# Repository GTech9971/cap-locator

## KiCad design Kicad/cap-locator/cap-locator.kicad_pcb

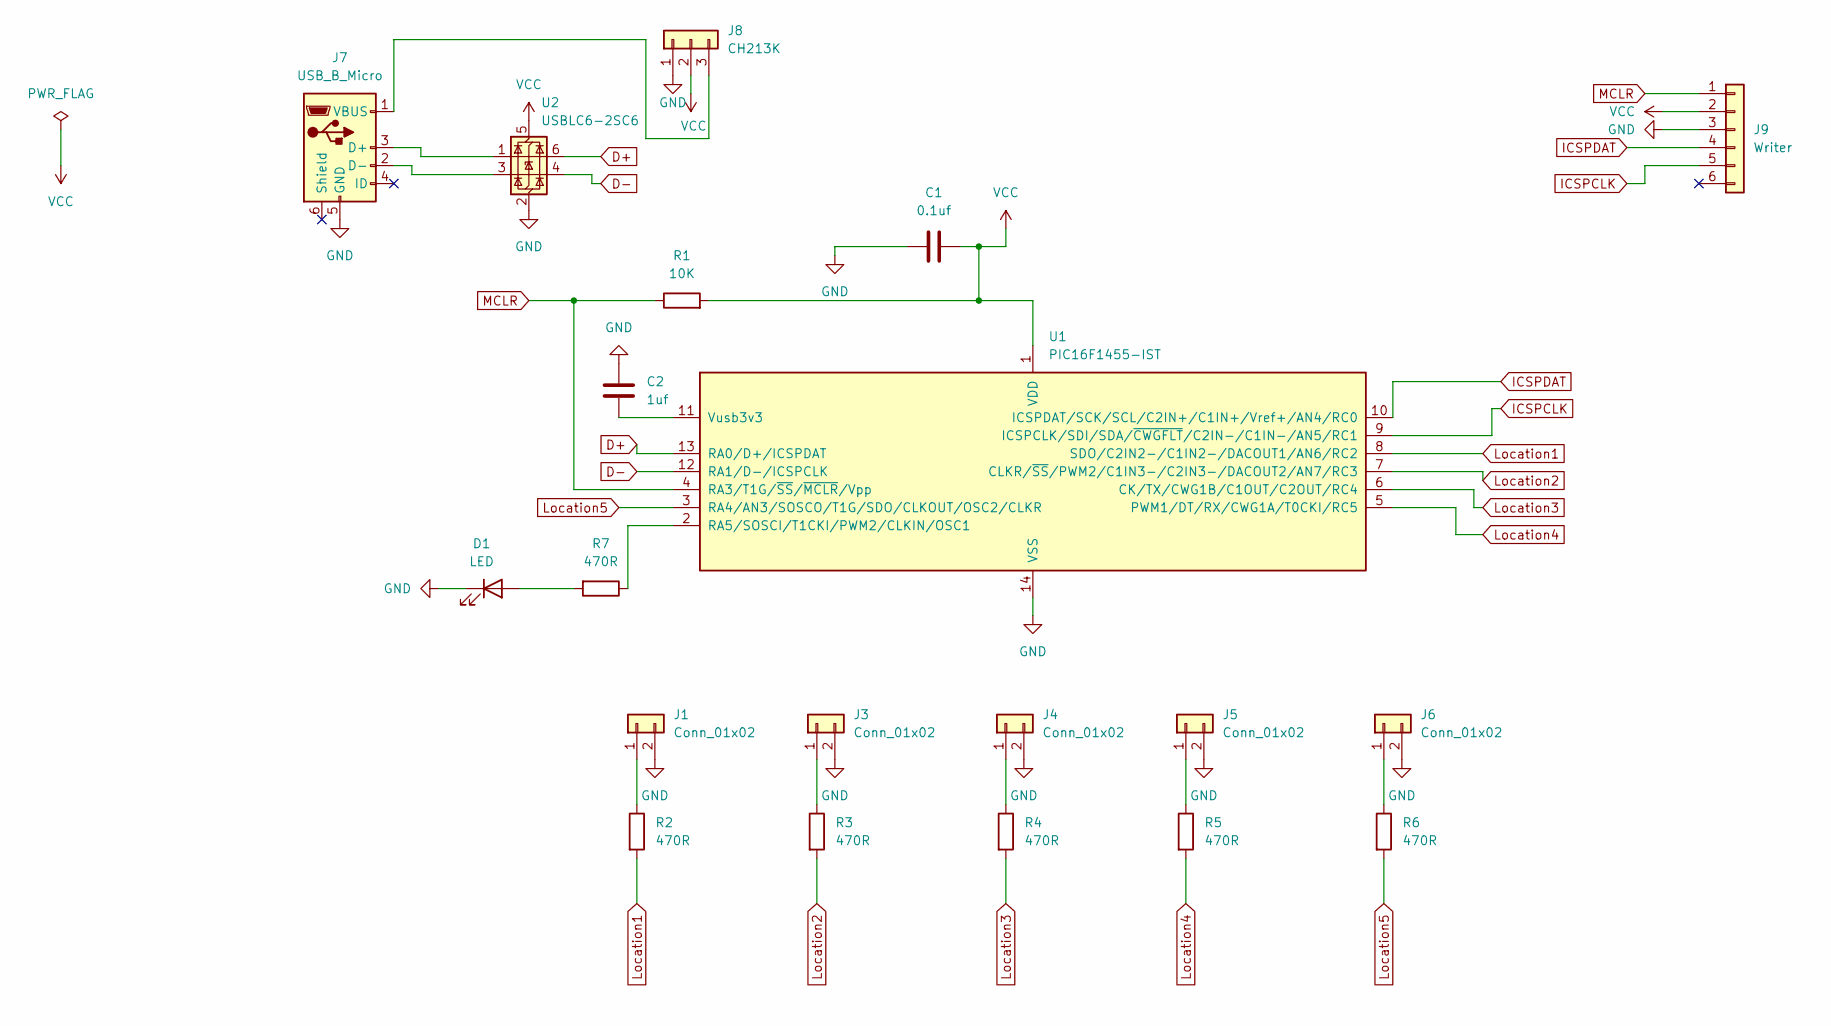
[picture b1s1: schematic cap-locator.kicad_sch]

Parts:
C1: 0.1uf; C_0603_1608Metric
C2: 1uf; C_0603_1608Metric
D1: LED; LED_0603_1608Metric
J1, J3, J4, J5, J6: Conn_01x02; JST_EH_S2B-EH_1x02_P2.50mm_Horizontal
J7: USB_B_Micro; USB_Micro-B_Molex_47346-0001
J8: CH213K; SOT-23-3
J9: Writer; PinSocket_1x06_P2.00mm_Horizontal
R1: 10K; R_0603_1608Metric
R2, R3, R4, R5, R6, R7: 470R; R_0603_1608Metric
U1: PIC16F1455-IST; TSSOP-14_4.4x5mm_P0.65mm
U2: USBLC6-2SC6; SOT-23-6

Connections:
D+: U1.13 (RA0/D+/ICSPDAT), U2.6 (I/O1)
D-: U1.12 (RA1/D-/ICSPCLK), U2.4 (I/O2)
GND: C1.1, C2.1, D1.1 (K), J1.2, J3.2, J4.2, J5.2, J6.2, J7.5 (GND), J8.1, J9.3, U1.14 (VSS), U2.2 (GND)
ICSPCLK: J9.5, U1.9 (ICSPCLK/SDI/SDA/~CWGFLT/C2IN-/C1IN-/AN5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)
ICSPDAT: J9.4, U1.10 (ICSPDAT/SCK/SCL/C2IN+/C1IN+/Vref+/AN4/R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)
Location1: R2.2, U1.8 (SDO/C2IN2-/C1IN2-/DACOUT1/AN6/RC2)
Location2: R3.2, U1.7 (CLKR/~SS/PWM2/C1IN3-/C2IN3-/DACOUT2/AN7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)
Location3: R4.2, U1.6 (CK/TX/CWG1B/C1OUT/C2OUT/RC4)
Location4: R5.2, U1.5 (PWM1/DT/RX/CWG1A/T0CKI/RC5)
Location5: R6.2, U1.3 (RA4/AN3/SOSCO/T1G/SDO/CLKOUT/OSC2/CLKR)
MCLR: J9.1, R1.1, U1.4 (RA3/T1G/~SS/~MCLR/Vpp)
unnamed: D1.2 (A), R7.2
unnamed: J1.1, R2.1
unnamed: J3.1, R3.1
unnamed: J4.1, R4.1
unnamed: J5.1, R5.1
unnamed: J6.1, R6.1
unnamed: J7.3 (D+), U2.1 (I/O1)
unnamed: J7.2 (D-), U2.3 (I/O2)
unnamed: J7.1 (VBUS), J8.3
unnamed: R7.1, U1.2 (RA5/SOSCI/T1CKI/PWM2/CLKIN/OSC1)
unnamed: C2.2, U1.11 (Vusb3v3)
VCC: C1.2, J8.2, J9.2, R1.2, U1.1 (VDD), U2.5 (VBUS)

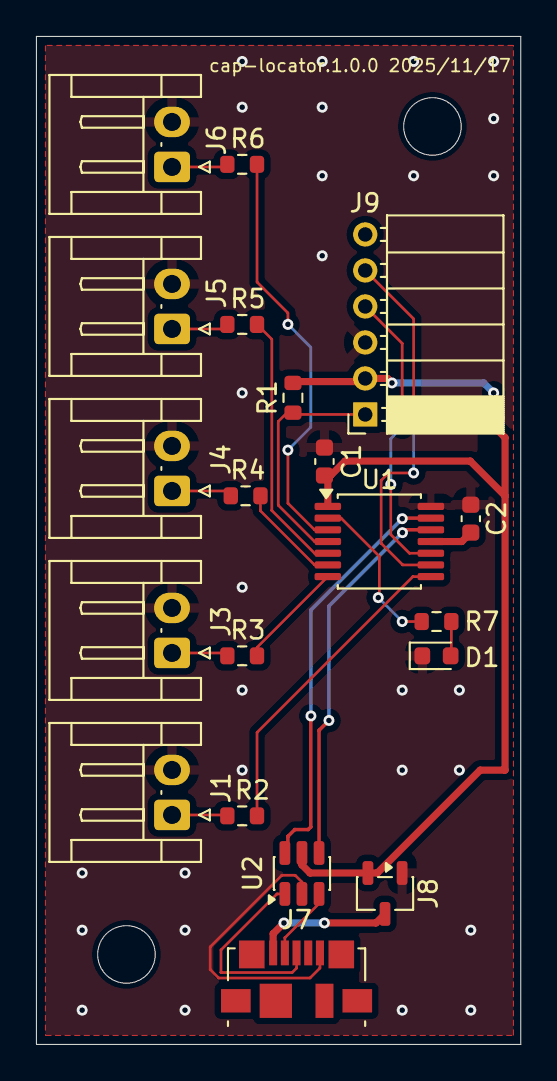
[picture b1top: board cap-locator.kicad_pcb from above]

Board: 2 copper layers, 26.9 x 56.0 mm, 22 parts (0 on the bottom side), 23 nets.

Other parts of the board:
MH1, MH2: MountingHole_3.2mm_M3

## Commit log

2025-11-11 kicadプロジェクト追加
2025-11-11 回路図記載
2025-11-17 基板発注
2025-11-29 Add Cap Locator HID firmware and docs
2025-11-30 Update LED pin mapping and Japanese README
2025-12-01 feature report廃止
2025-12-01 feature reportで使用していた不要コード削除
2025-12-05 デバイスにシリアル番号を追記
2025-12-05 バスパワーデバイスに修正
2025-12-30 起動時にステータスLEDが光るようにした
